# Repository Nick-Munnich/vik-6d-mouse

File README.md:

Simple draft of a 6d mouse VIK module concept.

Idea is to solder SMD nuts onto the inner 3 points, and then use those to stabilise the compression springs. Meanwhile the extension springs get hooked over the tabs on the ends and secured with a screw, washer, and nut.
All M2, of course. 

Magnet goes in the middle, and VIK cable just hangs down near it. Bottom design depends on the exact springs purchased I think.

Overall circular diameter is 45mm, inner circle diameter is 35mm.

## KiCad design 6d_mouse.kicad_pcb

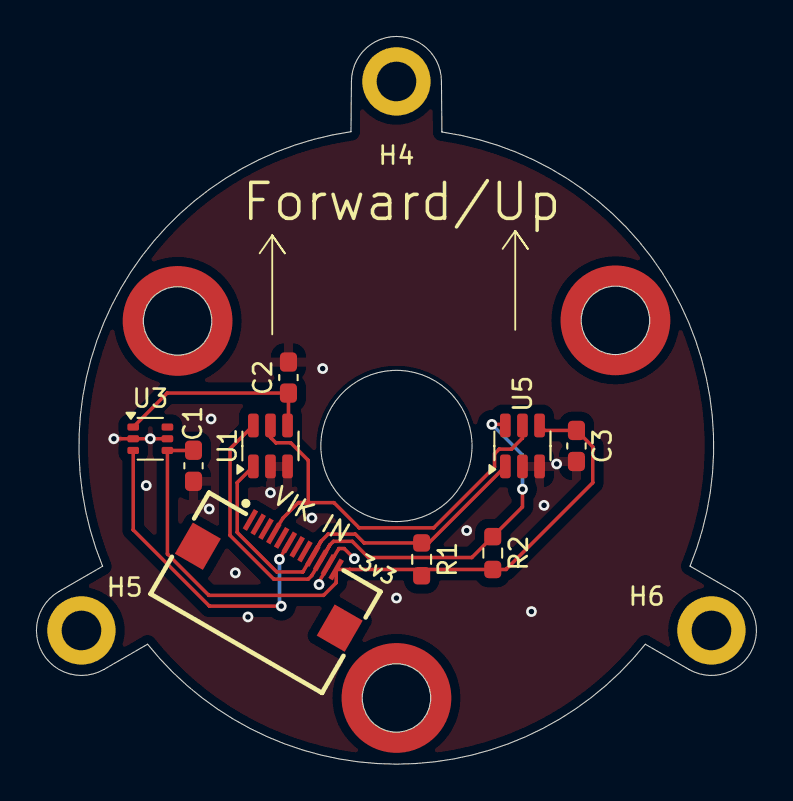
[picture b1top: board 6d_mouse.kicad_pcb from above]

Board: 2 copper layers, 40.0 x 40.4 mm, 15 parts (0 on the bottom side), 7 nets.

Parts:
C1: 1uF; C_0603_1608Metric_Pad1.08x0.95mm_HandSolder
C2, C3: 100nF; C_0603_1608Metric_Pad1.08x0.95mm_HandSolder
H1, H2, H3: Compression_Nut; MountingHole_M2_Pad_NonPTH_TopOnly
H4, H5, H6: Extension_Screw; MountingHole_2.2mm_M2_DIN965_Pad
J1: vik-module-connector; vik-module-connector-horizontal
R1, R2: 4.7K; R_0603_1608Metric_Pad0.98x0.95mm_HandSolder
U1, U5: TMAG5273; SOT-23-6
U3: SiP32431DR3; SOT-363_SC-70-6

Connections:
/INT: J1.4 (GP_AD2), U1.5 (INT), U5.5 (INT)
/S2_OE: J1.6 (GP_AD1), U3.3 (ON)
/SCL: J1.9 (SCL), R1.1, U1.1 (SCL), U5.1 (SCL)
/SDA: J1.10 (SDA), R2.1, U1.6 (SDA), U5.6 (SDA)
GND: C1.2, C2.2, C3.2, J1.11 (GND), U1.2 (GND), U1.3 (GND), U3.2 (GND), U3.5 (GND), U5.2 (GND), U5.3 (GND)
unnamed: C2.1, U1.4 (VCC), U3.1 (OUT)
VDD: C1.1, C3.1, J1.12 (3V3), R1.2, R2.2, U3.4 (IN), U5.4 (VCC)

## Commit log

2024-06-17 Initial draft, no pretties cos I'm bad
2024-06-17 removing useless files
2024-06-17 added readme
2024-06-17 added license
2024-06-17 fixed missing registers for I2C
2024-06-17 updated render
2024-06-18 changed to TMAG5273
